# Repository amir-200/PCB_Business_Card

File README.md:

# PCB_Business_Card

## Final requirements 

1. LED Matrix
2. Battery powered
3. PCB Edge USB-C Connector (For programming/ act as MSC (mass storage class) device to update content)
4. MSC(Mass Storage Class) device so the content of the display can be updated easily
5. Fluid Simulation
6. RTC
7. NFC
8. Provision for interfacing an OLED display 

## Technical Specs

1. Double sided 2 layer PCB
2. 252 LEDs (Yellow/ White)
4. TM1640 LED drive controller IC x 2
5. PCB Edge USB-C Connector 
6. RP2350A MCU 
7. ST25TN01K NFC Forum Type 2 Tag IC
8. TP4057 Linear battery charger
9. QMI8658 IMU 
10. External Flash 
11. LIR2032 Coin cell
12. MOQ : 5

## TODO 

[ ] USB circuitry  : Mihir

[ ] battery charging : amir

[ ] Card Controller foundation: RP2350A power, USB data, flash, I2C bus, Motion Wake interrupt, TM1640 control pins, debug/programming support, and optional power-status sensing

## Card Controller Interface Table

| Subsystem | Candidate part | Interface | Controller signals | Current decision |
| --- | --- | --- | --- | --- |
| Program flash and content storage | Winbond W25Q128JVSIQ, 16 MB | Dedicated RP2350A QSPI | QSPI SCLK, SS, SD0-SD3 | Use one flash with a firmware area and MSC-exposed content partition |
| LED matrix | TM1640 x2 | TM1640 two-wire control | Driver A CLK/DIO, Driver B CLK/DIO | 21 x 12 matrix split as top 6 rows and bottom 6 rows |
| RTC | DS3231 candidate | I2C | SDA, SCL | Revisit later; DS3231 is preferred over DS1307 for 3V3 operation |
| IMU | QMI8658 | I2C plus interrupt | SDA, SCL, IMU_INT | Use dedicated Motion Wake interrupt |
| NFC tag | ST25TN01K | I2C if MCU configuration is needed | SDA, SCL, optional interrupt | Keep on shared I2C unless address or datasheet review says otherwise |
| OLED provision | TBD OLED module | SPI preferred | SCLK, MOSI, CS, DC, RESET | Keep as provision/header; do not share this assumption with TM1640 control |
| USB update | PCB edge USB-C | USB 2.0 plus VBUS sense | USB_DP, USB_DM, VBUS_SENSE | USB exposes MSC content partition and powers/charges card |
| Debug and recovery | Pads plus tiny BOOTSEL button | SWD and boot/reset access | SWDIO, SWCLK, RUN pad, GND, 3V3, BOOTSEL button | Low-profile debug pads; one tiny BOOTSEL button |
| Battery status | TBD divider/switch | ADC sense | BATTERY_SENSE | Include power-conscious battery voltage measurement |

## Things to remember while laying out the pcb 

- the internal regulator component placement and the inductor orientation has to be same as the rasbeery pi  official doc
- AOTA-B201610S3R3-101-T this is the recommended inductor that the official docs recommend 
-  

## Collaboration

- Work on short feature branches for each hardware section, for example `feature/card-controller`.
- Only one person should edit the KiCad schematic/PCB files at a time.
- Push branches to GitHub and review changes before merging to `main`.
- Do not commit KiCad lock files, local history, generated DRC/ERC reports, or temporary files.

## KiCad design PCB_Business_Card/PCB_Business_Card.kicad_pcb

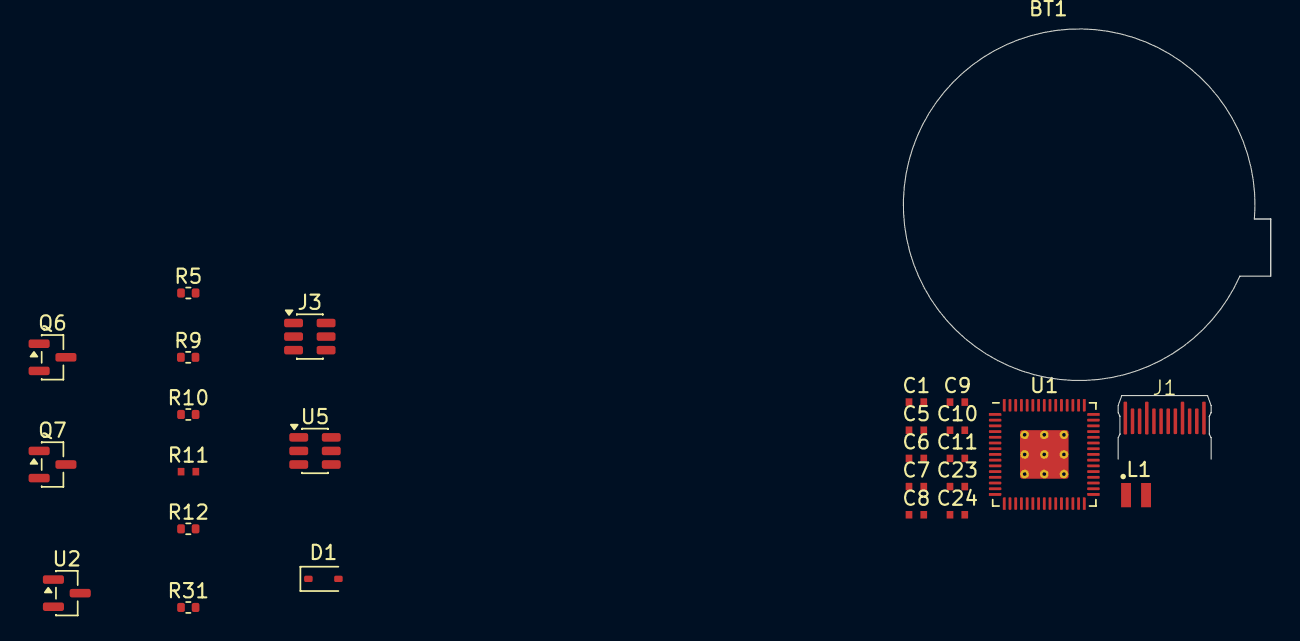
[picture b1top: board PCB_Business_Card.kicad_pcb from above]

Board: 2 copper layers, 25.7 x 30.1 mm, 26 parts (0 on the bottom side), 18 nets, no tracks yet.

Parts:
BT1: Battery_Cell; BatteryHolder_Custom
C1, C5, C24: 1u; C_0402_1005Metric_small_pads
C6, C7, C9, C10: 4.7u; C_0402_1005Metric_small_pads
C8, C11, C23: 100n; C_0402_1005Metric_small_pads
D1: Schottky Diode; D_SOD-323
J1: USB_C_Receptacle_USB2.0_14P; USB_C_PADDLE
J3: TP4057; SOT-23-6
L1: 3.3u; L_pol_2016
Q6, Q7: HL-2302V; SOT-23
R5: 33; R_0402_1005Metric
R9: 20K; R_0402_1005Metric
R10: 100; R_0402_1005Metric
R11: 5K1; C_0402_1005Metric_small_pads
R12: 5K1; R_0402_1005Metric
R31: 1K; R_0402_1005Metric
U1: RP2350A; RP2350-QFN-60-1EP_7x7_P0.4mm_EP3.4x3.4mm_ThermalVias
U2: REG_3.3V; SOT-23
U5: DW01A; SOT-23-6

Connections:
+1V1: C7.1, C8.1, C10.1, C11.1, L1.1, U1.6 (DVDD), U1.23 (DVDD), U1.39 (DVDD), U1.50 (VREG_FB)
+3V3: C5.1, C6.1, R5.1, U1.49 (VREG_VIN), U2.2 (VO)
/USB_D+: J1.A6 (D+), J1.B6 (D+)
/USB_D-: J1.A7 (D-), J1.B7 (D-)
/VREG_AVDD: C9.1, R5.2, U1.46 (VREG_AVDD)
/VREG_LX: L1.2, U1.48 (VREG_LX)
GND: C1.2, C5.2, C6.2, C7.2, C8.2, C9.2, C10.2, C11.2, C24.2, J1.A1 (GND), J1.A12 (GND), J1.B1 (GND), J1.B12 (GND), J3.2 (GND), J3.5 (STDBY), Q6.2 (S), R9.2, R11.2, R12.2, R31.1, U1.47 (VREG_PGND), U1.61 (GND), U2.1 (GND)
unnamed: BT1.1 (+), C24.1, D1.2 (A), J3.3 (BAT), R10.1
unnamed: BT1.2 (-), C23.2, Q7.2 (S), U5.6 (GND)
unnamed: J1.A5 (CC1), R11.1
unnamed: J1.B5 (CC2), R12.1
unnamed: J3.6 (PROG), R9.1
unnamed: Q6.3 (D), Q7.3 (D)
unnamed: Q6.1 (G), U5.3 (OC)
unnamed: Q7.1 (G), U5.1 (OD)
unnamed: R31.2, U5.2 (CS)
unnamed: C23.1, R10.2, U5.5 (VCC)
VBUS: C1.1, D1.1 (K), J1.A4 (VBUS), J1.A9 (VBUS), J1.B4 (VBUS), J1.B9 (VBUS), J3.4 (VCC), U2.3 (VI)

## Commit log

2026-06-02 Updated the README with the final requrements,Technical Specs
2026-06-02 added an empty kicad file
2026-06-03 Added USB and power circuitry, updated TP4056 -> TP4057
2026-06-05 chore: clean KiCad collaboration setup
2026-06-05 docs: define card controller interface map
2026-06-05 added the datasheet of tm1640 led driver ic and hardware guide of rp2350
2026-06-05 chore: ignore local reference repos
2026-06-08 feature progress : ok so i added the decoupling capacitors and the flash memory to the circuit a small part is remaining to complete the mcu section
2026-06-10 update: added the neccesary caps and resistors for the flash memory and the flash memory part is completed
